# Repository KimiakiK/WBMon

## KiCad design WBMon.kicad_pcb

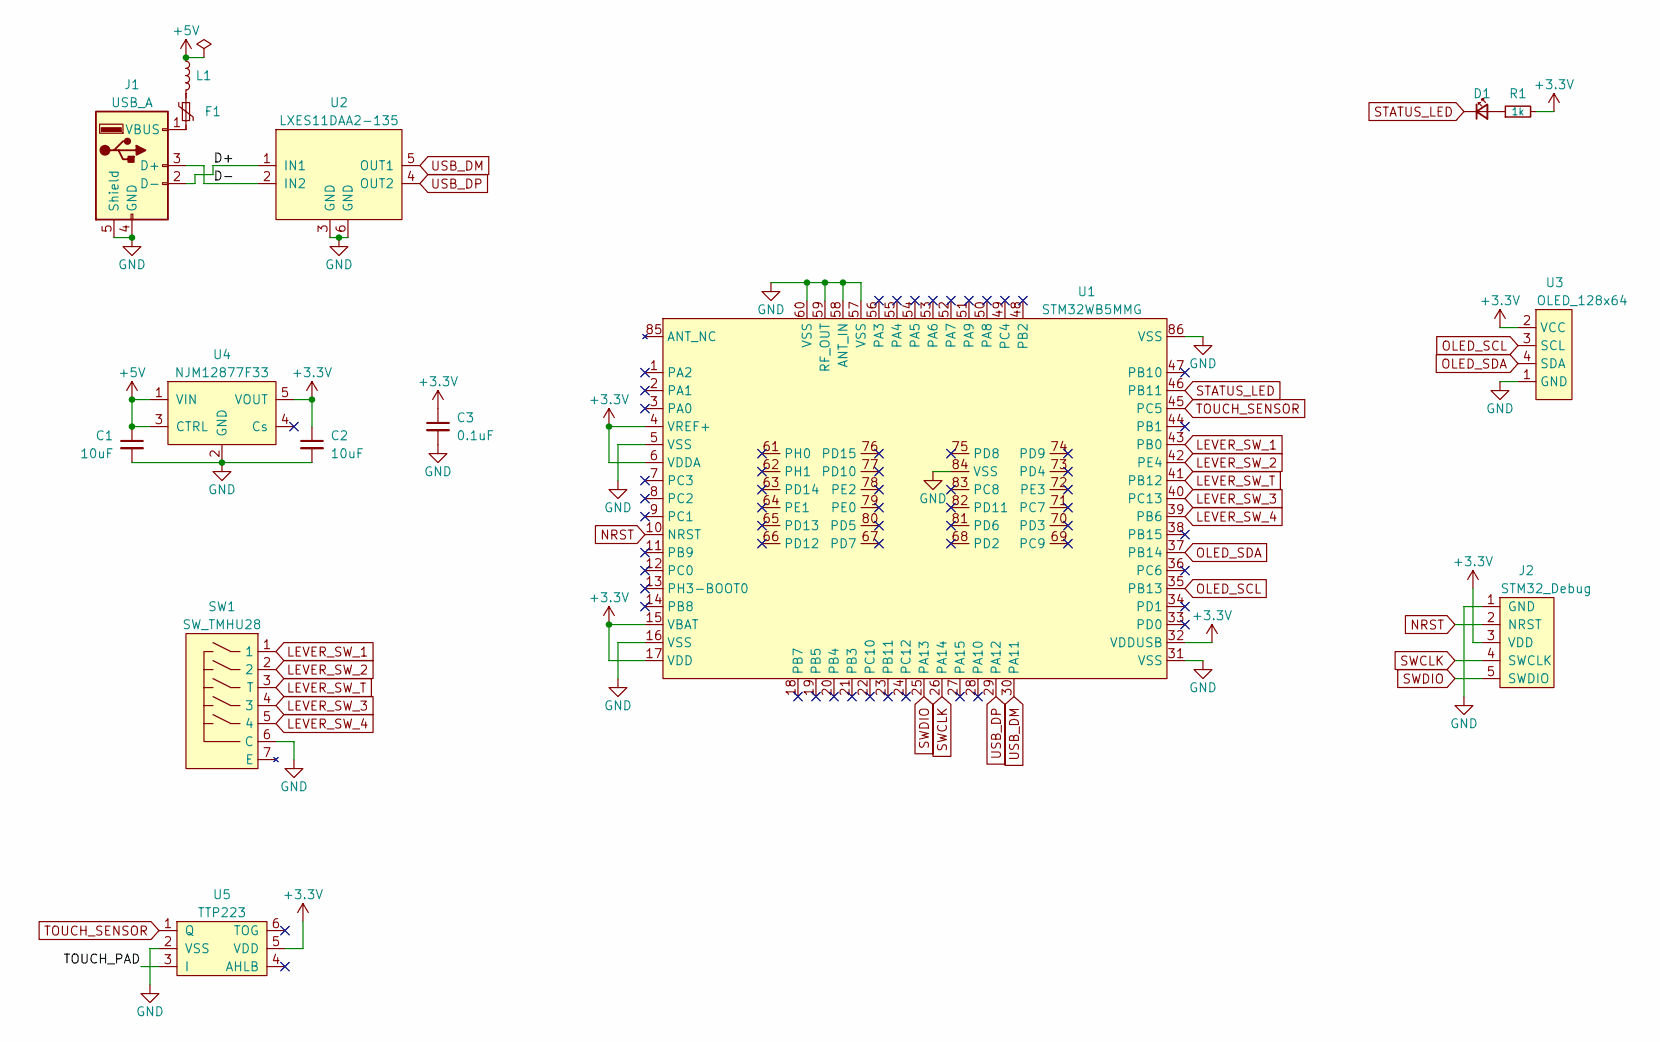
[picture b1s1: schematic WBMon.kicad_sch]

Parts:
C1, C2: 10uF; 1608Metric
C3: 0.1uF; 1005Metric
D1: LED; 1608Metric
F1: Polyfuse; 1608Metric
J1: USB_A; USB Type-A
J2: STM32_Debug; STM32_Debug_5pin
L1: L; 1608Metric
R1: 1k; 1608Metric
SW1: SW_TMHU28
U1: STM32WB5MMG
U2: LXES11DAA2-135; LXES11D
U3: OLED_128x64
U4: NJM12877F33; SOT-23-5
U5: TTP223; SOT-23-6

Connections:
+3.3V: C2.1, C3.1, J2.3 (VDD), R1.2, U1.4 (VREF+), U1.6 (VDDA), U1.15 (VBAT), U1.17 (VDD), U1.32 (VDDUSB), U3.2 (VCC), U4.5 (VOUT), U5.5 (VDD)
+5V: C1.1, L1.1, U4.1 (VIN), U4.3 (CTRL)
/D+: J1.2 (D-), U2.1 (IN1)
/D-: J1.3 (D+), U2.2 (IN2)
/TOUCH_PAD: U5.3 (I)
GND: C1.2, C2.2, C3.2, J1.4 (GND), J1.5 (Shield), J2.1 (GND), SW1.6 (C), U1.5 (VSS), U1.16 (VSS), U1.31 (VSS), U1.57 (VSS), U1.58 (ANT_IN), U1.59 (RF_OUT), U1.60 (VSS), U1.84 (VSS), U1.86 (VSS), U2.3 (GND), U2.6 (GND), U3.1 (GND), U4.2 (GND), U5.2 (VSS)
LEVER_SW_1: SW1.1, U1.43 (PB0)
LEVER_SW_2: SW1.2, U1.42 (PE4)
LEVER_SW_3: SW1.4 (3), U1.40 (PC13)
LEVER_SW_4: SW1.5 (4), U1.39 (PB6)
LEVER_SW_T: SW1.3 (T), U1.41 (PB12)
NRST: J2.2 (NRST), U1.10 (NRST)
unnamed: D1.2 (A), R1.1
unnamed: F1.1, L1.2
unnamed: F1.2, J1.1 (VBUS)
OLED_SCL: U1.35 (PB13), U3.3 (SCL)
OLED_SDA: U1.37 (PB14), U3.4 (SDA)
STATUS_LED: D1.1 (K), U1.46 (PB11)
SWCLK: J2.4 (SWCLK), U1.26 (PA14)
SWDIO: J2.5 (SWDIO), U1.25 (PA13)
TOUCH_SENSOR: U1.45 (PC5), U5.1 (Q)
USB_DM: U1.30 (PA11), U2.5 (OUT1)
USB_DP: U1.29 (PA12), U2.4 (OUT2)

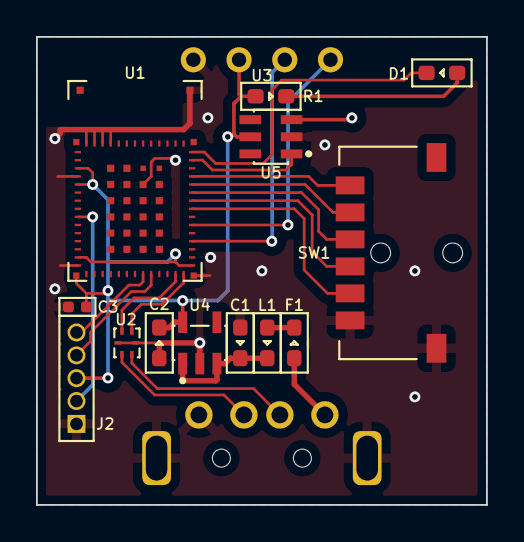
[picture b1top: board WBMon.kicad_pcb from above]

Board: 2 copper layers, 25.0 x 26.0 mm, 15 parts (1 on the bottom side), 22 nets.

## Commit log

2023-01-08 基板 V1.0
